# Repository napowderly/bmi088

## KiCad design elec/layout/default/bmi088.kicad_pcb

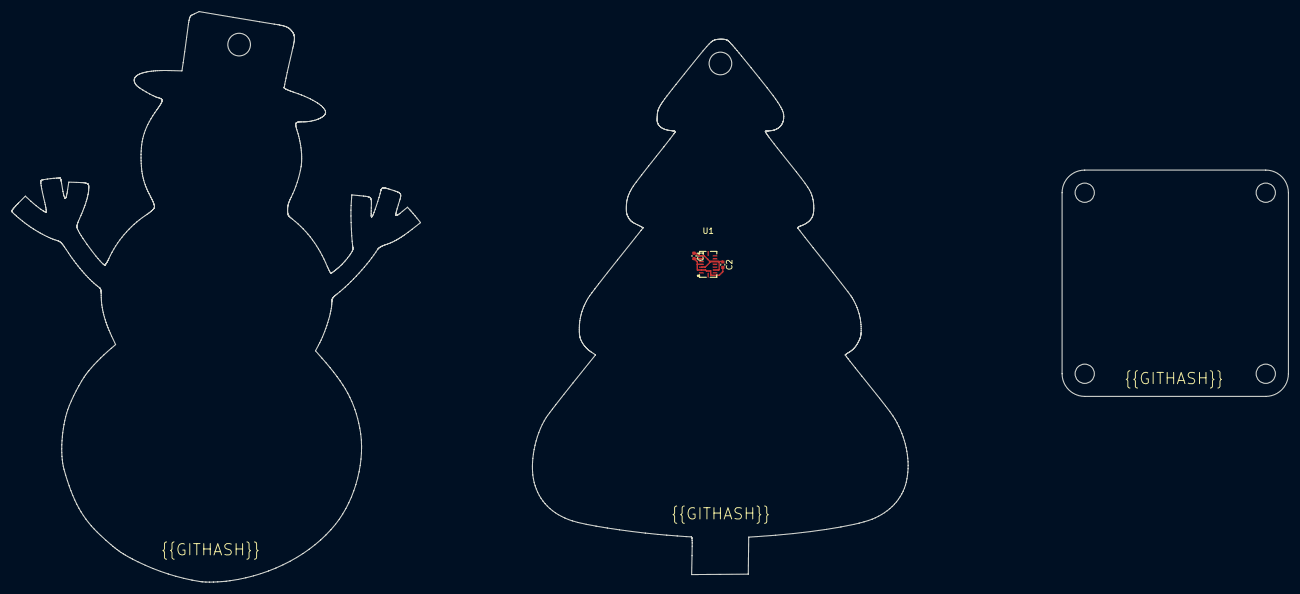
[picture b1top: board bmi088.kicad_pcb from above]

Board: 2 copper layers, 66.4 x 94.6 mm, 3 parts (0 on the bottom side), 2 nets.

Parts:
C1, C2: 16V 100nF X7R ±10% 0402 Multilayer Ceramic Capaci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; C0402
U1: LGA-16_L4.5-W3.0-P0.50-BL

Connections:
gnd: C1.2, C2.2, U1.2, U1.4, U1.6
vcc: C1.1, C2.1, U1.3, U1.7, U1.11, U1.14

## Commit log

2024-02-17 Configure project
2024-02-17 initial layout
2024-02-17 layout
2024-03-08 update layout
